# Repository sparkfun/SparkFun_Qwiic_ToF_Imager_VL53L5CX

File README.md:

SparkFun Qwiic ToF Imager with VL53L5CX
========================================

[*SparkFun Qwiic ToF Imager with VL53L5CX(SEN-18642)*](https://www.sparkfun.com/products/18642)

The SparkFun Qwiic ToF Imager is built around VL53L5CX from ST Electronics; a state of the art, Time-of-Flight (ToF), multizone ranging sensor enhancing the ST FlightSense product family. This chip integrates a SPAD array, physical infrared filters, and diffractive optical elements (DOE) to achieve the best ranging performance in various ambient lighting conditions with a range of cover glass materials. Utilizing our handy Qwiic system, no soldering is required to connect it to the rest of your system. However, we still have broken out 0.1"-spaced pins in case you prefer to use a breadboard.

Multizone distance measurements are possible up to 8x8 zones with a wide 63° diagonal FoV which can be reduced by software. Thanks to ST Histogram patented algorithms, the VL53L5CX is able to detect different objects within the FoV. The Histogram also provides immunity to cover glass crosstalk beyond 60 cm.

Ideal for 3D room mapping, obstacle detection for robotics, gesture recognition, IoT, laser-assisted autofocus, and AR/VR enhancement, the Qwiic connector on this sensor makes integration easy. 

SparkFun labored with love to create this code. Feel like supporting open source hardware? 
Buy a [breakout board](https://www.sparkfun.com/products/14722) from SparkFun!

Repository Contents
-------------------

* **/Documents** - Datasheet and User Manual
* **/Hardware** - Eagle design files (.brd, .sch)

Documentation
--------------
* **[Arduino Library](https://github.com/sparkfun/SparkFun_VL53L5CX_Arduino_Library)** - Library for reading distance in millimeters, signal rate, status, etc.
* **[Hookup Guide](https://learn.sparkfun.com/tutorials/qwiic-tof-imager---vl53l5cx-hookup-guide)** - Hookup guide for the Qwiic ToF Imager VL53L5CX

License Information
-------------------

This product is _**open source**_! 

Please review the LICENSE.md file for license information. 

If you have any questions or concerns on licensing, please contact techsupport@sparkfun.com.

Please use, reuse, and modify these files as you see fit. Please maintain attribution to SparkFun Electronics and release any derivative under the same license.

Distributed as-is; no warranty is given.

- Your friends at SparkFun.

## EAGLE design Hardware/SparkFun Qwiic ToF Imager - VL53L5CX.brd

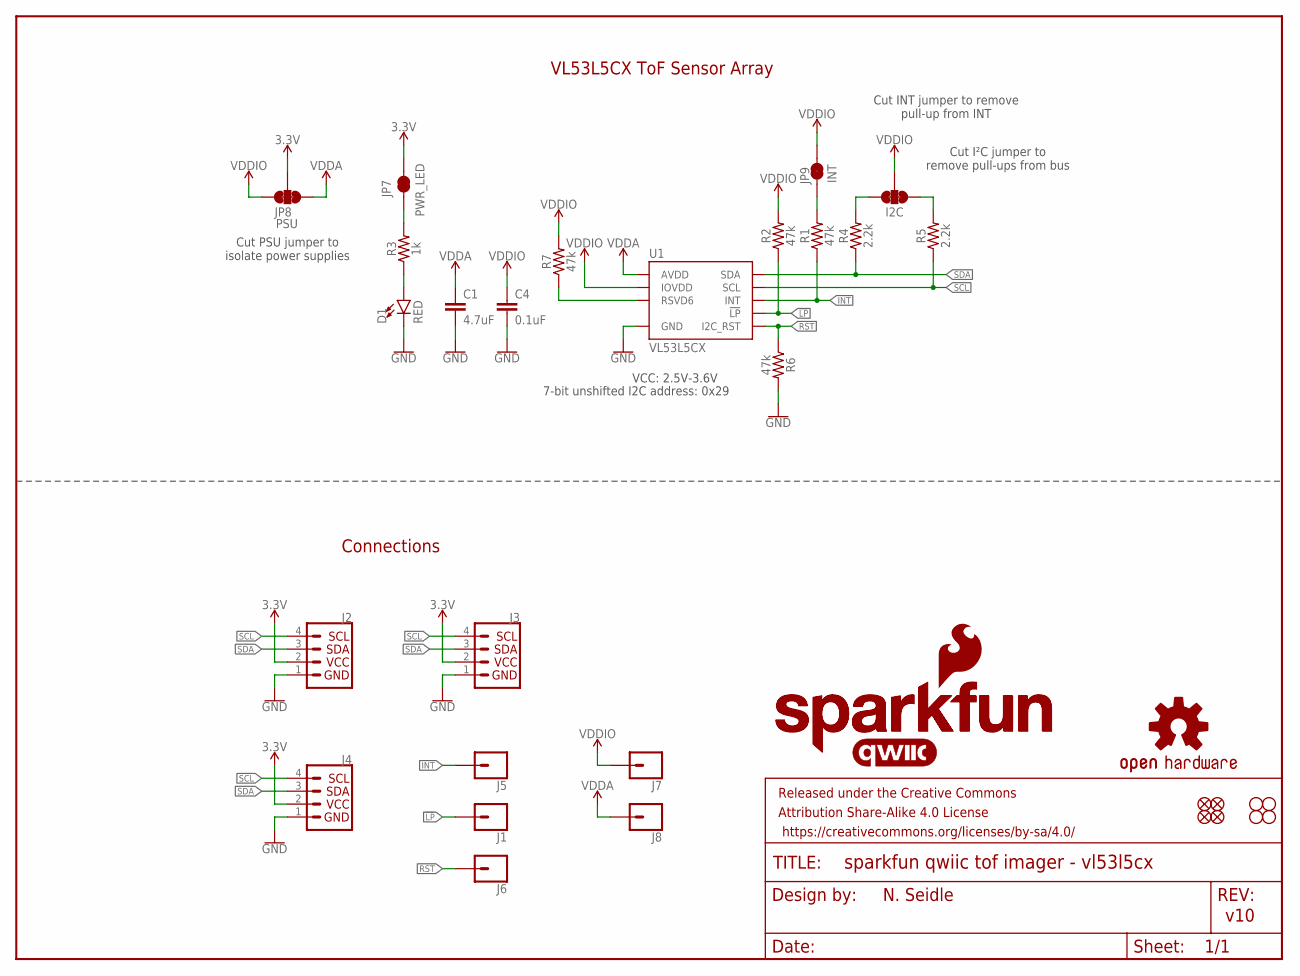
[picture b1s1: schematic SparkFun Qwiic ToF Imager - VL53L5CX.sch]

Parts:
C1: 4.7uF; 0603
C4: 0.1uF; 0603
D1: RED; LED-0603
FRAME1: FRAME-LETTER; CREATIVE_COMMONS
I2C: JUMPER-SMT_3_2-NC_TRACE_SILK; SMT-JUMPER_3_2-NC_TRACE_SILK
J1, J5, J6, J7, J8: CONN_01PTH_NO_SILK_YES_STOP; 1X01_NO_SILK
J2, J4: QWIIC_CONNECTORJS-1MM; JST04_1MM_RA
J3: PTH; 1X04_NO_SILK
JP1, JP2, JP5, JP6: FIDUCIALUFIDUCIAL; MICRO-FIDUCIAL
JP3, JP4, JP10, JP11: STAND-OFF
JP7: PWR_LED; SMT-JUMPER_2_NC_TRACE_SILK
JP8: PSU; SMT-JUMPER_3_2-NC_TRACE_SILK
JP9: INT; SMT-JUMPER_2_NC_TRACE_SILK
LOGO1: OSHW-LOGOMINI; OSHW-LOGO-MINI
LOGO3: QWIIC_LOGO_CONNECTOR; QWIIC_5.5MM
R1, R2, R6, R7: 47k; 0603
R3: 1k; 0603
R4, R5: 2.2k; 0603
U1: VL53L5CX
U$1: SFE_LOGO_NAME.1_INCH; SFE_LOGO_NAME_.1
U$2: SFE_LOGO_NAME_FLAME.1_INCH; SFE_LOGO_NAME_FLAME_.1

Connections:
3.3V: J2.2, J3.2 (VCC), J4.2, JP7.2, JP8.2
!LP: J1.1, R2.1, U1.A5 (!LP)
GND: C1.2, C4.2, D1.C, J2.1, J3.1 (GND), J4.1, R6.2, U1.A2 (GND), U1.A6 (GND), U1.A7 (GND), U1.B4 (GND), U1.C1 (GND), U1.C6 (GND), U1.C7 (GND)
INT: J5.1, R1.1, U1.A3 (INT)
unnamed: I2C.1, R5.2
unnamed: I2C.3, R4.2
unnamed: D1.A, R3.1
unnamed: JP9.1, R1.2
unnamed: JP7.1, R3.2
unnamed: R7.1, U1.C2 (RSVD6)
RST: J6.1, R6.1, U1.A1 (I2C_RST)
SCL: J2.4, J3.4 (SCL), J4.4, R5.1, U1.C4 (SCL)
SDA: J2.3, J3.3 (SDA), J4.3, R4.1, U1.C3 (SDA)
VDDA: C1.1, J8.1, JP8.1, U1.B1 (AVDD), U1.B7 (AVDD)
VDDIO: C4.1, I2C.2, J7.1, JP8.3, JP9.2, R2.2, R7.2, U1.A4 (IOVDD)

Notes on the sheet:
N. Seidle
v10
7-bit unshifted I2C address: 0x29
Cut I²C jumper to remove pull-ups from bus
Cut INT jumper to remove pull-up from INT
VCC: 2.5V-3.6V
VL53L5CX ToF Sensor Array
Cut PSU jumper to isolate power supplies
Connections

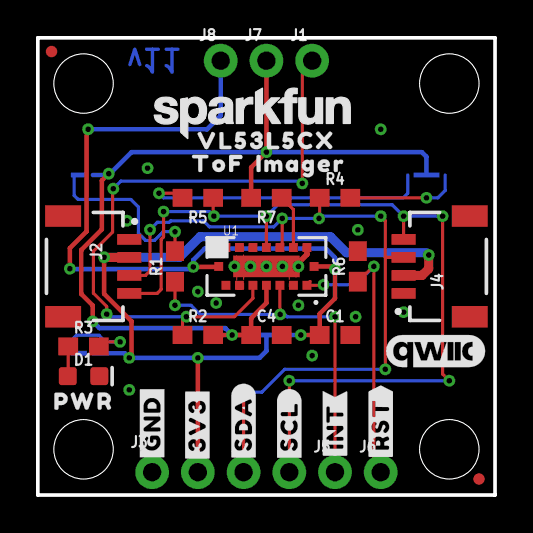
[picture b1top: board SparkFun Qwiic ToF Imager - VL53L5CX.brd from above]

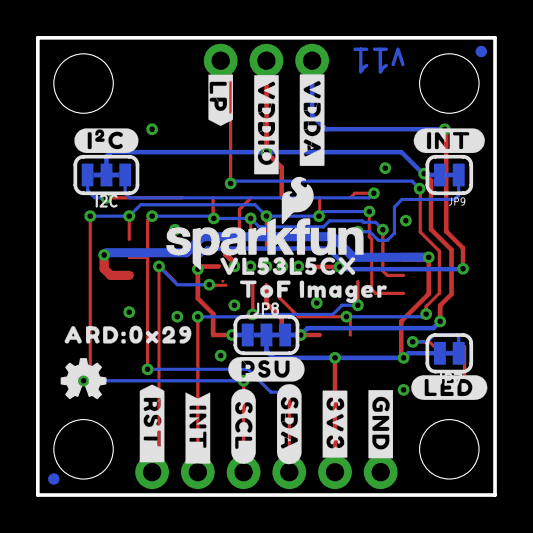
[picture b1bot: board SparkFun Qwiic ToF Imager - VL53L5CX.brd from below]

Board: 2 copper layers, 25.4 x 25.4 mm, 63 parts (25 on the bottom side), 15 nets.

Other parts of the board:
U$3, U$21: #3V3#13
U$4: PWR12
U$5: #LED#10
U$6: #INT#0
U$7: #RST#1
U$8: #INT_#0
U$9: #RST_#1
U$10: ##LP##2
U$11: #INT#1
U$12: #VDDA#0
U$14: #VDDIO#1
U$15: #PSU#0
U$16: #I�C#0
U$17, U$19: VL53L5CX0
U$18, U$22: IMAGER2
U$20, U$23: TOF1
U$24: #SCL#1
U$25: #SDA#0
U$26, U$30: #GND#62130
U$27: ARD#0X290
U$28: #SDA#62131
U$29: #SCL#62132

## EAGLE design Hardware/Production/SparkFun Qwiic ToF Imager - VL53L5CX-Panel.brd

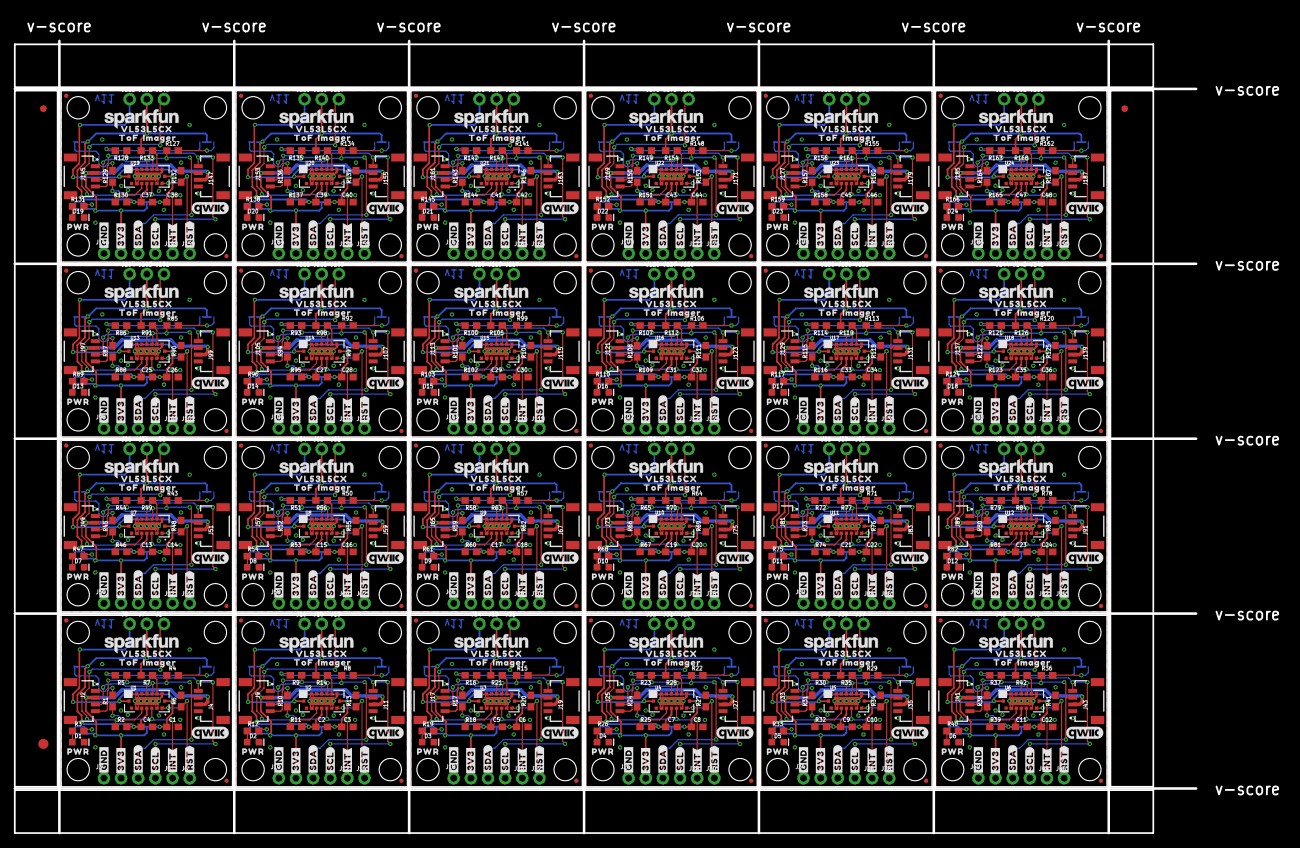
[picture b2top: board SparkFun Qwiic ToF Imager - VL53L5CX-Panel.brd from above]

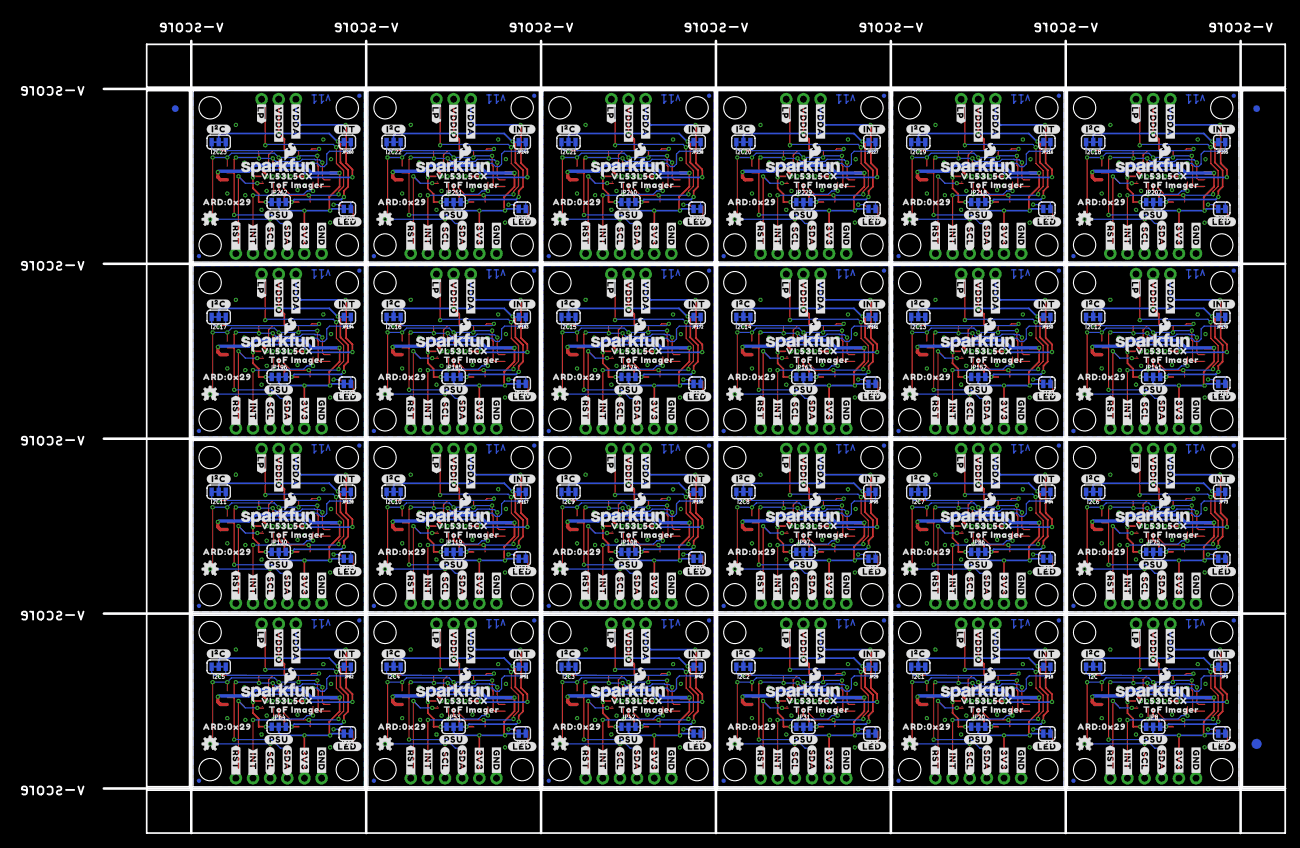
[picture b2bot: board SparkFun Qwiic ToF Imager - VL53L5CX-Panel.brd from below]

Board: 2 copper layers, 188.2 x 121.2 mm, 1494 parts (603 on the bottom side), 360 nets.

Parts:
C1, C3, C6, C8, C10, C12, C14, C16, C18, C20, C22, C24, C26, C28, C30, C32, C34, C36, C38, C40, C42, C44, C46, C48: 4.7uF; 0603
C2, C4, C5, C7, C9, C11, C13, C15, C17, C19, C21, C23, C25, C27, C29, C31, C33, C35, C37, C39, C41, C43, C45, C47: 0.1uF; 0603
D1, D2, D3, D4, D5, D6, D7, D8, D9, D10, D11, D12, D13, D14, D15, D16, D17, D18, D19, D20, D21, D22, D23, D24: RED; LED-0603
E$1, E$2, E$3, E$4: FIDUCIAL-1X2
E$5, E$6: FIDUCIAL-1.5X3
I2C, I2C1, I2C2, I2C3, I2C4, I2C5, I2C6, I2C7, I2C8, I2C9, I2C10, I2C11, I2C12, I2C13, I2C14, I2C15, I2C16, I2C17, I2C18, I2C19, I2C20, I2C21, I2C22, I2C23: JUMPER-SMT_3_2-NC_TRACE_SILK; SMT-JUMPER_3_2-NC_TRACE_SILK
J1, J5, J6, J7, J8, J12, J13, J14, J15, J16, J20, J21, J22, J23, J24, J28, J29, J30, J31, J32, J36, J37, J38, J39, J40, J44, J45, J46, J47, J48, J52, J53, J54, J55, J56, J60, J61, J62, J63, J64, J68, J69, J70, J71, J72, J76, J77, J78, J79, J80, J84, J85, J86, J87, J88, J92, J93, J94, J95, J96, J100, J101, J102, J103, J104, J108, J109, J110, J111, J112, J116, J117, J118, J119, J120, J124, J125, J126, J127, J128, J132, J133, J134, J135, J136, J140, J141, J142, J143, J144, J148, J149, J150, J151, J152, J156, J157, J158, J159, J160, J164, J165, J166, J167, J168, J172, J173, J174, J175, J176, J180, J181, J182, J183, J184, J188, J189, J190, J191, J192: 1X01_NO_SILK
J2, J4, J9, J11, J17, J19, J25, J27, J33, J35, J41, J43, J49, J51, J57, J59, J65, J67, J73, J75, J81, J83, J89, J91, J97, J99, J105, J107, J113, J115, J121, J123, J129, J131, J137, J139, J145, J147, J153, J155, J161, J163, J169, J171, J177, J179, J185, J187: JST04_1MM_RA
J3, J10, J18, J26, J34, J42, J50, J58, J66, J74, J82, J90, J98, J106, J114, J122, J130, J138, J146, J154, J162, J170, J178, J186: PTH; 1X04_NO_SILK
JP1, JP2, JP5, JP6, JP14, JP15, JP16, JP17, JP25, JP26, JP27, JP28, JP36, JP37, JP38, JP39, JP47, JP48, JP49, JP50, JP58, JP59, JP60, JP61, JP69, JP70, JP71, JP72, JP80, JP81, JP82, JP83, JP91, JP92, JP93, JP94, JP102, JP103, JP104, JP105, JP113, JP114, JP115, JP116, JP124, JP125, JP126, JP127, JP135, JP136, JP137, JP138, JP146, JP147, JP148, JP149, JP157, JP158, JP159, JP160, JP168, JP169, JP170, JP171, JP179, JP180, JP181, JP182, JP190, JP191, JP192, JP193, JP201, JP202, JP203, JP204, JP212, JP213, JP214, JP215, JP223, JP224, JP225, JP226, JP234, JP235, JP236, JP237, JP245, JP246, JP247, JP248, JP256, JP257, JP258, JP259: FIDUCIALUFIDUCIAL; MICRO-FIDUCIAL
JP3, JP4, JP10, JP11, JP12, JP13, JP21, JP22, JP23, JP24, JP32, JP33, JP34, JP35, JP43, JP44, JP45, JP46, JP54, JP55, JP56, JP57, JP65, JP66, JP67, JP68, JP76, JP77, JP78, JP79, JP87, JP88, JP89, JP90, JP98, JP99, JP100, JP101, JP109, JP110, JP111, JP112, JP120, JP121, JP122, JP123, JP131, JP132, JP133, JP134, JP142, JP143, JP144, JP145, JP153, JP154, JP155, JP156, JP164, JP165, JP166, JP167, JP175, JP176, JP177, JP178, JP186, JP187, JP188, JP189, JP197, JP198, JP199, JP200, JP208, JP209, JP210, JP211, JP219, JP220, JP221, JP222, JP230, JP231, JP232, JP233, JP241, JP242, JP243, JP244, JP252, JP253, JP254, JP255, JP263, JP264: STAND-OFF
JP7, JP19, JP30, JP41, JP52, JP63, JP74, JP85, JP96, JP107, JP118, JP129, JP140, JP151, JP162, JP173, JP184, JP195, JP206, JP217, JP228, JP239, JP250, JP261: PWR_LED; SMT-JUMPER_2_NC_TRACE_SILK
JP8, JP20, JP31, JP42, JP53, JP64, JP75, JP86, JP97, JP108, JP119, JP130, JP141, JP152, JP163, JP174, JP185, JP196, JP207, JP218, JP229, JP240, JP251, JP262: PSU; SMT-JUMPER_3_2-NC_TRACE_SILK
JP9, JP18, JP29, JP40, JP51, JP62, JP73, JP84, JP95, JP106, JP117, JP128, JP139, JP150, JP161, JP172, JP183, JP194, JP205, JP216, JP227, JP238, JP249, JP260: INT; SMT-JUMPER_2_NC_TRACE_SILK
LOGO1, LOGO2, LOGO5, LOGO7, LOGO9, LOGO11, LOGO13, LOGO15, LOGO17, LOGO19, LOGO21, LOGO23, LOGO25, LOGO27, LOGO29, LOGO31, LOGO33, LOGO35, LOGO37, LOGO39, LOGO41, LOGO43, LOGO45, LOGO47: OSHW-LOGOMINI; OSHW-LOGO-MINI
LOGO3, LOGO4, LOGO6, LOGO8, LOGO10, LOGO12, LOGO14, LOGO16, LOGO18, LOGO20, LOGO22, LOGO24, LOGO26, LOGO28, LOGO30, LOGO32, LOGO34, LOGO36, LOGO38, LOGO40, LOGO42, LOGO44, LOGO46, LOGO48: QWIIC_LOGO_CONNECTOR; QWIIC_5.5MM
R1, R2, R6, R7, R10, R11, R13, R14, R17, R18, R20, R21, R24, R25, R27, R28, R31, R32, R34, R35, R38, R39, R41, R42, R45, R46, R48, R49, R52, R53, R55, R56, R59, R60, R62, R63, R66, R67, R69, R70, R73, R74, R76, R77, R80, R81, R83, R84, R87, R88, R90, R91, R94, R95, R97, R98, R101, R102, R104, R105, R108, R109, R111, R112, R115, R116, R118, R119, R122, R123, R125, R126, R129, R130, R132, R133, R136, R137, R139, R140, R143, R144, R146, R147, R150, R151, R153, R154, R157, R158, R160, R161, R164, R165, R167, R168: 47k; 0603
R3, R12, R19, R26, R33, R40, R47, R54, R61, R68, R75, R82, R89, R96, R103, R110, R117, R124, R131, R138, R145, R152, R159, R166: 1k; 0603
R4, R5, R8, R9, R15, R16, R22, R23, R29, R30, R36, R37, R43, R44, R50, R51, R57, R58, R64, R65, R71, R72, R78, R79, R85, R86, R92, R93, R99, R100, R106, R107, R113, R114, R120, R121, R127, R128, R134, R135, R141, R142, R148, R149, R155, R156, R162, R163: 2.2k; 0603
U1, U2, U3, U4, U5, U6, U7, U8, U9, U10, U11, U12, U13, U14, U15, U16, U17, U18, U19, U20, U21, U22, U23, U24: VL53L5CX
U$1, U$31, U$60, U$89, U$118, U$147, U$176, U$205, U$234, U$263, U$292, U$321, U$350, U$379, U$408, U$437, U$466, U$495, U$524, U$553, U$582, U$611, U$640, U$669: SFE_LOGO_NAME.1_INCH; SFE_LOGO_NAME_.1
U$2, U$13, U$59, U$88, U$117, U$146, U$175, U$204, U$233, U$262, U$291, U$320, U$349, U$378, U$407, U$436, U$465, U$494, U$523, U$552, U$581, U$610, U$639, U$668: SFE_LOGO_NAME_FLAME.1_INCH; SFE_LOGO_NAME_FLAME_.1
U$3, U$21, U$36, U$37, U$65, U$66, U$94, U$95, U$123, U$124, U$152, U$153, U$181, U$182, U$210, U$211, U$239, U$240, U$268, U$269, U$297, U$298, U$326, U$327, U$355, U$356, U$384, U$385, U$413, U$414, U$442, U$443, U$471, U$472, U$500, U$501, U$529, U$530, U$558, U$559, U$587, U$588, U$616, U$617, U$645, U$646, U$674, U$675: #3V3#13
U$4, U$38, U$67, U$96, U$125, U$154, U$183, U$212, U$241, U$270, U$299, U$328, U$357, U$386, U$415, U$444, U$473, U$502, U$531, U$560, U$589, U$618, U$647, U$676: PWR12
U$5, U$39, U$68, U$97, U$126, U$155, U$184, U$213, U$242, U$271, U$300, U$329, U$358, U$387, U$416, U$445, U$474, U$503, U$532, U$561, U$590, U$619, U$648, U$677: #LED#10
U$6, U$40, U$69, U$98, U$127, U$156, U$185, U$214, U$243, U$272, U$301, U$330, U$359, U$388, U$417, U$446, U$475, U$504, U$533, U$562, U$591, U$620, U$649, U$678: #INT#0
U$7, U$41, U$70, U$99, U$128, U$157, U$186, U$215, U$244, U$273, U$302, U$331, U$360, U$389, U$418, U$447, U$476, U$505, U$534, U$563, U$592, U$621, U$650, U$679: #RST#1
U$8, U$42, U$71, U$100, U$129, U$158, U$187, U$216, U$245, U$274, U$303, U$332, U$361, U$390, U$419, U$448, U$477, U$506, U$535, U$564, U$593, U$622, U$651, U$680: #INT_#0
U$9, U$43, U$72, U$101, U$130, U$159, U$188, U$217, U$246, U$275, U$304, U$333, U$362, U$391, U$420, U$449, U$478, U$507, U$536, U$565, U$594, U$623, U$652, U$681: #RST_#1
U$10, U$44, U$73, U$102, U$131, U$160, U$189, U$218, U$247, U$276, U$305, U$334, U$363, U$392, U$421, U$450, U$479, U$508, U$537, U$566, U$595, U$624, U$653, U$682: ##LP##2
U$11, U$51, U$80, U$109, U$138, U$167, U$196, U$225, U$254, U$283, U$312, U$341, U$370, U$399, U$428, U$457, U$486, U$515, U$544, U$573, U$602, U$631, U$660, U$689: #INT#1
U$12, U$45, U$74, U$103, U$132, U$161, U$190, U$219, U$248, U$277, U$306, U$335, U$364, U$393, U$422, U$451, U$480, U$509, U$538, U$567, U$596, U$625, U$654, U$683: #VDDA#0
U$14, U$46, U$75, U$104, U$133, U$162, U$191, U$220, U$249, U$278, U$307, U$336, U$365, U$394, U$423, U$452, U$481, U$510, U$539, U$568, U$597, U$626, U$655, U$684: #VDDIO#1
U$15, U$52, U$81, U$110, U$139, U$168, U$197, U$226, U$255, U$284, U$313, U$342, U$371, U$400, U$429, U$458, U$487, U$516, U$545, U$574, U$603, U$632, U$661, U$690: #PSU#0
U$16, U$50, U$79, U$108, U$137, U$166, U$195, U$224, U$253, U$282, U$311, U$340, U$369, U$398, U$427, U$456, U$485, U$514, U$543, U$572, U$601, U$630, U$659, U$688: #I�C#0
U$17, U$19, U$47, U$53, U$76, U$82, U$105, U$111, U$134, U$140, U$163, U$169, U$192, U$198, U$221, U$227, U$250, U$256, U$279, U$285, U$308, U$314, U$337, U$343, U$366, U$372, U$395, U$401, U$424, U$430, U$453, U$459, U$482, U$488, U$511, U$517, U$540, U$546, U$569, U$575, U$598, U$604, U$627, U$633, U$656, U$662, U$685, U$691: VL53L5CX0
U$18, U$22, U$48, U$55, U$77, U$84, U$106, U$113, U$135, U$142, U$164, U$171, U$193, U$200, U$222, U$229, U$251, U$258, U$280, U$287, U$309, U$316, U$338, U$345, U$367, U$374, U$396, U$403, U$425, U$432, U$454, U$461, U$483, U$490, U$512, U$519, U$541, U$548, U$570, U$577, U$599, U$606, U$628, U$635, U$657, U$664, U$686, U$693: IMAGER2
U$20, U$23, U$49, U$54, U$78, U$83, U$107, U$112, U$136, U$141, U$165, U$170, U$194, U$199, U$223, U$228, U$252, U$257, U$281, U$286, U$310, U$315, U$339, U$344, U$368, U$373, U$397, U$402, U$426, U$431, U$455, U$460, U$484, U$489, U$513, U$518, U$542, U$547, U$571, U$576, U$600, U$605, U$629, U$634, U$658, U$663, U$687, U$692: TOF1
U$24, U$56, U$85, U$114, U$143, U$172, U$201, U$230, U$259, U$288, U$317, U$346, U$375, U$404, U$433, U$462, U$491, U$520, U$549, U$578, U$607, U$636, U$665, U$694: #SCL#1
U$25, U$57, U$86, U$115, U$144, U$173, U$202, U$231, U$260, U$289, U$318, U$347, U$376, U$405, U$434, U$463, U$492, U$521, U$550, U$579, U$608, U$637, U$666, U$695: #SDA#0
U$26, U$30, U$32, U$35, U$61, U$64, U$90, U$93, U$119, U$122, U$148, U$151, U$177, U$180, U$206, U$209, U$235, U$238, U$264, U$267, U$293, U$296, U$322, U$325, U$351, U$354, U$380, U$383, U$409, U$412, U$438, U$441, U$467, U$470, U$496, U$499, U$525, U$528, U$554, U$557, U$583, U$586, U$612, U$615, U$641, U$644, U$670, U$673: #GND#62130
U$27, U$58, U$87, U$116, U$145, U$174, U$203, U$232, U$261, U$290, U$319, U$348, U$377, U$406, U$435, U$464, U$493, U$522, U$551, U$580, U$609, U$638, U$667, U$696: ARD#0X290
U$28, U$33, U$62, U$91, U$120, U$149, U$178, U$207, U$236, U$265, U$294, U$323, U$352, U$381, U$410, U$439, U$468, U$497, U$526, U$555, U$584, U$613, U$642, U$671: #SDA#62131
U$29, U$34, U$63, U$92, U$121, U$150, U$179, U$208, U$237, U$266, U$295, U$324, U$353, U$382, U$411, U$440, U$469, U$498, U$527, U$556, U$585, U$614, U$643, U$672: #SCL#62132

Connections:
3.3V: J2.2, J3.2, J4.2, JP7.2, JP8.2
3.3V1: J9.2, J10.2, J11.2, JP19.2, JP20.2
3.3V2: J17.2, J18.2, J19.2, JP30.2, JP31.2
3.3V3: J25.2, J26.2, J27.2, JP41.2, JP42.2
3.3V4: J33.2, J34.2, J35.2, JP52.2, JP53.2
3.3V5: J41.2, J42.2, J43.2, JP63.2, JP64.2
3.3V6: J49.2, J50.2, J51.2, JP74.2, JP75.2
3.3V7: J57.2, J58.2, J59.2, JP85.2, JP86.2
3.3V8: J65.2, J66.2, J67.2, JP96.2, JP97.2
3.3V9: J73.2, J74.2, J75.2, JP107.2, JP108.2
3.3V10: J81.2, J82.2, J83.2, JP118.2, JP119.2
3.3V11: J89.2, J90.2, J91.2, JP129.2, JP130.2
3.3V12: J97.2, J98.2, J99.2, JP140.2, JP141.2
3.3V13: J105.2, J106.2, J107.2, JP151.2, JP152.2
3.3V14: J113.2, J114.2, J115.2, JP162.2, JP163.2
3.3V15: J121.2, J122.2, J123.2, JP173.2, JP174.2
3.3V16: J129.2, J130.2, J131.2, JP184.2, JP185.2
3.3V17: J137.2, J138.2, J139.2, JP195.2, JP196.2
3.3V18: J145.2, J146.2, J147.2, JP206.2, JP207.2
3.3V19: J153.2, J154.2, J155.2, JP217.2, JP218.2
3.3V20: J161.2, J162.2, J163.2, JP228.2, JP229.2
3.3V21: J169.2, J170.2, J171.2, JP239.2, JP240.2
3.3V22: J177.2, J178.2, J179.2, JP250.2, JP251.2
3.3V23: J185.2, J186.2, J187.2, JP261.2, JP262.2
!LP: J1.1, R2.1, U1.A5
!LP1: J13.1, R11.1, U2.A5
!LP2: J21.1, R18.1, U3.A5
!LP3: J29.1, R25.1, U4.A5
!LP4: J37.1, R32.1, U5.A5
!LP5: J45.1, R39.1, U6.A5
!LP6: J53.1, R46.1, U7.A5
!LP7: J61.1, R53.1, U8.A5
!LP8: J69.1, R60.1, U9.A5
!LP9: J77.1, R67.1, U10.A5
!LP10: J85.1, R74.1, U11.A5
!LP11: J93.1, R81.1, U12.A5
!LP12: J101.1, R88.1, U13.A5
!LP13: J109.1, R95.1, U14.A5
!LP14: J117.1, R102.1, U15.A5
!LP15: J125.1, R109.1, U16.A5
!LP16: J133.1, R116.1, U17.A5
!LP17: J141.1, R123.1, U18.A5
!LP18: J149.1, R130.1, U19.A5
!LP19: J157.1, R137.1, U20.A5
!LP20: J165.1, R144.1, U21.A5
!LP21: J173.1, R151.1, U22.A5
!LP22: J181.1, R158.1, U23.A5
!LP23: J189.1, R165.1, U24.A5
GND: C1.2, C4.2, D1.C, J2.1, J3.1, J4.1, R6.2, U1.A2, U1.A6, U1.A7, U1.B4, U1.C1, U1.C6, U1.C7
GND1: C2.2, C3.2, D2.C, J9.1, J10.1, J11.1, R13.2, U2.A2, U2.A6, U2.A7, U2.B4, U2.C1, U2.C6, U2.C7
GND2: C5.2, C6.2, D3.C, J17.1, J18.1, J19.1, R20.2, U3.A2, U3.A6, U3.A7, U3.B4, U3.C1, U3.C6, U3.C7
GND3: C7.2, C8.2, D4.C, J25.1, J26.1, J27.1, R27.2, U4.A2, U4.A6, U4.A7, U4.B4, U4.C1, U4.C6, U4.C7
GND4: C9.2, C10.2, D5.C, J33.1, J34.1, J35.1, R34.2, U5.A2, U5.A6, U5.A7, U5.B4, U5.C1, U5.C6, U5.C7
GND5: C11.2, C12.2, D6.C, J41.1, J42.1, J43.1, R41.2, U6.A2, U6.A6, U6.A7, U6.B4, U6.C1, U6.C6, U6.C7
GND6: C13.2, C14.2, D7.C, J49.1, J50.1, J51.1, R48.2, U7.A2, U7.A6, U7.A7, U7.B4, U7.C1, U7.C6, U7.C7
GND7: C15.2, C16.2, D8.C, J57.1, J58.1, J59.1, R55.2, U8.A2, U8.A6, U8.A7, U8.B4, U8.C1, U8.C6, U8.C7
GND8: C17.2, C18.2, D9.C, J65.1, J66.1, J67.1, R62.2, U9.A2, U9.A6, U9.A7, U9.B4, U9.C1, U9.C6, U9.C7
GND9: C19.2, C20.2, D10.C, J73.1, J74.1, J75.1, R69.2, U10.A2, U10.A6, U10.A7, U10.B4, U10.C1, U10.C6, U10.C7
GND10: C21.2, C22.2, D11.C, J81.1, J82.1, J83.1, R76.2, U11.A2, U11.A6, U11.A7, U11.B4, U11.C1, U11.C6, U11.C7
GND11: C23.2, C24.2, D12.C, J89.1, J90.1, J91.1, R83.2, U12.A2, U12.A6, U12.A7, U12.B4, U12.C1, U12.C6, U12.C7
GND12: C25.2, C26.2, D13.C, J97.1, J98.1, J99.1, R90.2, U13.A2, U13.A6, U13.A7, U13.B4, U13.C1, U13.C6, U13.C7
GND13: C27.2, C28.2, D14.C, J105.1, J106.1, J107.1, R97.2, U14.A2, U14.A6, U14.A7, U14.B4, U14.C1, U14.C6, U14.C7
GND14: C29.2, C30.2, D15.C, J113.1, J114.1, J115.1, R104.2, U15.A2, U15.A6, U15.A7, U15.B4, U15.C1, U15.C6, U15.C7
GND15: C31.2, C32.2, D16.C, J121.1, J122.1, J123.1, R111.2, U16.A2, U16.A6, U16.A7, U16.B4, U16.C1, U16.C6, U16.C7
GND16: C33.2, C34.2, D17.C, J129.1, J130.1, J131.1, R118.2, U17.A2, U17.A6, U17.A7, U17.B4, U17.C1, U17.C6, U17.C7
GND17: C35.2, C36.2, D18.C, J137.1, J138.1, J139.1, R125.2, U18.A2, U18.A6, U18.A7, U18.B4, U18.C1, U18.C6, U18.C7
GND18: C37.2, C38.2, D19.C, J145.1, J146.1, J147.1, R132.2, U19.A2, U19.A6, U19.A7, U19.B4, U19.C1, U19.C6, U19.C7
GND19: C39.2, C40.2, D20.C, J153.1, J154.1, J155.1, R139.2, U20.A2, U20.A6, U20.A7, U20.B4, U20.C1, U20.C6, U20.C7
GND20: C41.2, C42.2, D21.C, J161.1, J162.1, J163.1, R146.2, U21.A2, U21.A6, U21.A7, U21.B4, U21.C1, U21.C6, U21.C7
GND21: C43.2, C44.2, D22.C, J169.1, J170.1, J171.1, R153.2, U22.A2, U22.A6, U22.A7, U22.B4, U22.C1, U22.C6, U22.C7
GND22: C45.2, C46.2, D23.C, J177.1, J178.1, J179.1, R160.2, U23.A2, U23.A6, U23.A7, U23.B4, U23.C1, U23.C6, U23.C7
GND23: C47.2, C48.2, D24.C, J185.1, J186.1, J187.1, R167.2, U24.A2, U24.A6, U24.A7, U24.B4, U24.C1, U24.C6, U24.C7
INT: J5.1, R1.1, U1.A3
INT1: J12.1, R10.1, U2.A3
INT2: J20.1, R17.1, U3.A3
INT3: J28.1, R24.1, U4.A3
INT4: J36.1, R31.1, U5.A3
INT5: J44.1, R38.1, U6.A3
INT6: J52.1, R45.1, U7.A3
INT7: J60.1, R52.1, U8.A3
INT8: J68.1, R59.1, U9.A3
INT9: J76.1, R66.1, U10.A3
INT10: J84.1, R73.1, U11.A3
INT11: J92.1, R80.1, U12.A3
INT12: J100.1, R87.1, U13.A3
INT13: J108.1, R94.1, U14.A3
INT14: J116.1, R101.1, U15.A3
INT15: J124.1, R108.1, U16.A3
INT16: J132.1, R115.1, U17.A3
INT17: J140.1, R122.1, U18.A3
INT18: J148.1, R129.1, U19.A3
INT19: J156.1, R136.1, U20.A3
INT20: J164.1, R143.1, U21.A3
INT21: J172.1, R150.1, U22.A3
INT22: J180.1, R157.1, U23.A3
INT23: J188.1, R164.1, U24.A3
unnamed: I2C.1, R5.2
unnamed: I2C.3, R4.2
unnamed: D1.A, R3.1
unnamed: JP9.1, R1.2
unnamed: JP7.1, R3.2
unnamed: R7.1, U1.C2
unnamed: I2C1.1, R9.2
unnamed: I2C1.3, R8.2
unnamed: JP18.1, R10.2
unnamed: D2.A, R12.1
unnamed: JP19.1, R12.2
unnamed: R14.1, U2.C2
unnamed: I2C2.1, R16.2
unnamed: I2C2.3, R15.2
unnamed: JP29.1, R17.2
unnamed: D3.A, R19.1
unnamed: JP30.1, R19.2
unnamed: R21.1, U3.C2
unnamed: I2C3.1, R23.2
unnamed: I2C3.3, R22.2
unnamed: JP40.1, R24.2
unnamed: D4.A, R26.1
unnamed: JP41.1, R26.2
unnamed: R28.1, U4.C2
unnamed: I2C4.1, R30.2
unnamed: I2C4.3, R29.2
unnamed: JP51.1, R31.2
unnamed: D5.A, R33.1
unnamed: JP52.1, R33.2
unnamed: R35.1, U5.C2
unnamed: I2C5.1, R37.2
unnamed: I2C5.3, R36.2
unnamed: JP62.1, R38.2
unnamed: D6.A, R40.1
unnamed: JP63.1, R40.2
unnamed: R42.1, U6.C2
unnamed: I2C6.1, R44.2
unnamed: I2C6.3, R43.2
unnamed: JP73.1, R45.2
unnamed: D7.A, R47.1
unnamed: JP74.1, R47.2
unnamed: R49.1, U7.C2
unnamed: I2C7.1, R51.2
unnamed: I2C7.3, R50.2
unnamed: JP84.1, R52.2
unnamed: D8.A, R54.1
unnamed: JP85.1, R54.2
unnamed: R56.1, U8.C2
unnamed: I2C8.1, R58.2
unnamed: I2C8.3, R57.2
unnamed: JP95.1, R59.2
unnamed: D9.A, R61.1
unnamed: JP96.1, R61.2
unnamed: R63.1, U9.C2
unnamed: I2C9.1, R65.2
unnamed: I2C9.3, R64.2
unnamed: JP106.1, R66.2
unnamed: D10.A, R68.1
unnamed: JP107.1, R68.2
unnamed: R70.1, U10.C2
unnamed: I2C10.1, R72.2
unnamed: I2C10.3, R71.2
unnamed: JP117.1, R73.2
unnamed: D11.A, R75.1
unnamed: JP118.1, R75.2
unnamed: R77.1, U11.C2
unnamed: I2C11.1, R79.2
unnamed: I2C11.3, R78.2
unnamed: JP128.1, R80.2
unnamed: D12.A, R82.1
unnamed: JP129.1, R82.2
unnamed: R84.1, U12.C2
unnamed: I2C12.1, R86.2
unnamed: I2C12.3, R85.2
unnamed: JP139.1, R87.2
unnamed: D13.A, R89.1
unnamed: JP140.1, R89.2
unnamed: R91.1, U13.C2
unnamed: I2C13.1, R93.2
unnamed: I2C13.3, R92.2
unnamed: JP150.1, R94.2
unnamed: D14.A, R96.1
unnamed: JP151.1, R96.2
unnamed: R98.1, U14.C2
unnamed: I2C14.1, R100.2
unnamed: I2C14.3, R99.2
unnamed: JP161.1, R101.2
unnamed: D15.A, R103.1
unnamed: JP162.1, R103.2
unnamed: R105.1, U15.C2
unnamed: I2C15.1, R107.2
unnamed: I2C15.3, R106.2
unnamed: JP172.1, R108.2
unnamed: D16.A, R110.1
unnamed: JP173.1, R110.2
unnamed: R112.1, U16.C2
unnamed: I2C16.1, R114.2
unnamed: I2C16.3, R113.2
unnamed: JP183.1, R115.2
unnamed: D17.A, R117.1
unnamed: JP184.1, R117.2
unnamed: R119.1, U17.C2
unnamed: I2C17.1, R121.2
unnamed: I2C17.3, R120.2
unnamed: JP194.1, R122.2
unnamed: D18.A, R124.1
unnamed: JP195.1, R124.2
unnamed: R126.1, U18.C2
unnamed: I2C18.1, R128.2
unnamed: I2C18.3, R127.2
unnamed: JP205.1, R129.2
unnamed: D19.A, R131.1
unnamed: JP206.1, R131.2
unnamed: R133.1, U19.C2
unnamed: I2C19.1, R135.2
unnamed: I2C19.3, R134.2
unnamed: JP216.1, R136.2
unnamed: D20.A, R138.1
unnamed: JP217.1, R138.2
unnamed: R140.1, U20.C2
unnamed: I2C20.1, R142.2
unnamed: I2C20.3, R141.2
unnamed: JP227.1, R143.2
unnamed: D21.A, R145.1
unnamed: JP228.1, R145.2
unnamed: R147.1, U21.C2
unnamed: I2C21.1, R149.2
unnamed: I2C21.3, R148.2
unnamed: JP238.1, R150.2
unnamed: D22.A, R152.1
unnamed: JP239.1, R152.2
unnamed: R154.1, U22.C2
unnamed: I2C22.1, R156.2
unnamed: I2C22.3, R155.2
unnamed: JP249.1, R157.2
unnamed: D23.A, R159.1
unnamed: JP250.1, R159.2
unnamed: R161.1, U23.C2
unnamed: I2C23.1, R163.2
unnamed: I2C23.3, R162.2
unnamed: JP260.1, R164.2
unnamed: D24.A, R166.1
unnamed: JP261.1, R166.2
unnamed: R168.1, U24.C2
RST: J6.1, R6.1, U1.A1
RST1: J14.1, R13.1, U2.A1
RST2: J22.1, R20.1, U3.A1
RST3: J30.1, R27.1, U4.A1
RST4: J38.1, R34.1, U5.A1
RST5: J46.1, R41.1, U6.A1
RST6: J54.1, R48.1, U7.A1
RST7: J62.1, R55.1, U8.A1
RST8: J70.1, R62.1, U9.A1
RST9: J78.1, R69.1, U10.A1
RST10: J86.1, R76.1, U11.A1
RST11: J94.1, R83.1, U12.A1
RST12: J102.1, R90.1, U13.A1
RST13: J110.1, R97.1, U14.A1
RST14: J118.1, R104.1, U15.A1
RST15: J126.1, R111.1, U16.A1
RST16: J134.1, R118.1, U17.A1
RST17: J142.1, R125.1, U18.A1
RST18: J150.1, R132.1, U19.A1
RST19: J158.1, R139.1, U20.A1
RST20: J166.1, R146.1, U21.A1
RST21: J174.1, R153.1, U22.A1
RST22: J182.1, R160.1, U23.A1
RST23: J190.1, R167.1, U24.A1
SCL: J2.4, J3.4, J4.4, R5.1, U1.C4
SCL1: J9.4, J10.4, J11.4, R9.1, U2.C4
SCL2: J17.4, J18.4, J19.4, R16.1, U3.C4
SCL3: J25.4, J26.4, J27.4, R23.1, U4.C4
SCL4: J33.4, J34.4, J35.4, R30.1, U5.C4
SCL5: J41.4, J42.4, J43.4, R37.1, U6.C4
SCL6: J49.4, J50.4, J51.4, R44.1, U7.C4
SCL7: J57.4, J58.4, J59.4, R51.1, U8.C4
SCL8: J65.4, J66.4, J67.4, R58.1, U9.C4
SCL9: J73.4, J74.4, J75.4, R65.1, U10.C4
SCL10: J81.4, J82.4, J83.4, R72.1, U11.C4
SCL11: J89.4, J90.4, J91.4, R79.1, U12.C4
SCL12: J97.4, J98.4, J99.4, R86.1, U13.C4
SCL13: J105.4, J106.4, J107.4, R93.1, U14.C4
SCL14: J113.4, J114.4, J115.4, R100.1, U15.C4
SCL15: J121.4, J122.4, J123.4, R107.1, U16.C4
SCL16: J129.4, J130.4, J131.4, R114.1, U17.C4
SCL17: J137.4, J138.4, J139.4, R121.1, U18.C4
SCL18: J145.4, J146.4, J147.4, R128.1, U19.C4
SCL19: J153.4, J154.4, J155.4, R135.1, U20.C4
SCL20: J161.4, J162.4, J163.4, R142.1, U21.C4
SCL21: J169.4, J170.4, J171.4, R149.1, U22.C4
SCL22: J177.4, J178.4, J179.4, R156.1, U23.C4
SCL23: J185.4, J186.4, J187.4, R163.1, U24.C4
SDA: J2.3, J3.3, J4.3, R4.1, U1.C3
SDA1: J9.3, J10.3, J11.3, R8.1, U2.C3
SDA2: J17.3, J18.3, J19.3, R15.1, U3.C3
SDA3: J25.3, J26.3, J27.3, R22.1, U4.C3
SDA4: J33.3, J34.3, J35.3, R29.1, U5.C3
SDA5: J41.3, J42.3, J43.3, R36.1, U6.C3
SDA6: J49.3, J50.3, J51.3, R43.1, U7.C3
SDA7: J57.3, J58.3, J59.3, R50.1, U8.C3
SDA8: J65.3, J66.3, J67.3, R57.1, U9.C3
SDA9: J73.3, J74.3, J75.3, R64.1, U10.C3
SDA10: J81.3, J82.3, J83.3, R71.1, U11.C3
SDA11: J89.3, J90.3, J91.3, R78.1, U12.C3
SDA12: J97.3, J98.3, J99.3, R85.1, U13.C3
SDA13: J105.3, J106.3, J107.3, R92.1, U14.C3
SDA14: J113.3, J114.3, J115.3, R99.1, U15.C3
SDA15: J121.3, J122.3, J123.3, R106.1, U16.C3
SDA16: J129.3, J130.3, J131.3, R113.1, U17.C3
SDA17: J137.3, J138.3, J139.3, R120.1, U18.C3
SDA18: J145.3, J146.3, J147.3, R127.1, U19.C3
SDA19: J153.3, J154.3, J155.3, R134.1, U20.C3
SDA20: J161.3, J162.3, J163.3, R141.1, U21.C3
SDA21: J169.3, J170.3, J171.3, R148.1, U22.C3
SDA22: J177.3, J178.3, J179.3, R155.1, U23.C3
SDA23: J185.3, J186.3, J187.3, R162.1, U24.C3
VDDA: C1.1, J8.1, JP8.1, U1.B1, U1.B7
VDDA1: C3.1, J16.1, JP20.1, U2.B1, U2.B7
VDDA2: C6.1, J24.1, JP31.1, U3.B1, U3.B7
VDDA3: C8.1, J32.1, JP42.1, U4.B1, U4.B7
VDDA4: C10.1, J40.1, JP53.1, U5.B1, U5.B7
VDDA5: C12.1, J48.1, JP64.1, U6.B1, U6.B7
VDDA6: C14.1, J56.1, JP75.1, U7.B1, U7.B7
VDDA7: C16.1, J64.1, JP86.1, U8.B1, U8.B7
VDDA8: C18.1, J72.1, JP97.1, U9.B1, U9.B7
VDDA9: C20.1, J80.1, JP108.1, U10.B1, U10.B7
VDDA10: C22.1, J88.1, JP119.1, U11.B1, U11.B7
VDDA11: C24.1, J96.1, JP130.1, U12.B1, U12.B7
VDDA12: C26.1, J104.1, JP141.1, U13.B1, U13.B7
VDDA13: C28.1, J112.1, JP152.1, U14.B1, U14.B7
VDDA14: C30.1, J120.1, JP163.1, U15.B1, U15.B7
VDDA15: C32.1, J128.1, JP174.1, U16.B1, U16.B7
VDDA16: C34.1, J136.1, JP185.1, U17.B1, U17.B7
VDDA17: C36.1, J144.1, JP196.1, U18.B1, U18.B7
VDDA18: C38.1, J152.1, JP207.1, U19.B1, U19.B7
VDDA19: C40.1, J160.1, JP218.1, U20.B1, U20.B7
VDDA20: C42.1, J168.1, JP229.1, U21.B1, U21.B7
VDDA21: C44.1, J176.1, JP240.1, U22.B1, U22.B7
VDDA22: C46.1, J184.1, JP251.1, U23.B1, U23.B7
VDDA23: C48.1, J192.1, JP262.1, U24.B1, U24.B7
VDDIO: C4.1, I2C.2, J7.1, JP8.3, JP9.2, R2.2, R7.2, U1.A4
VDDIO1: C2.1, I2C1.2, J15.1, JP18.2, JP20.3, R11.2, R14.2, U2.A4
VDDIO2: C5.1, I2C2.2, J23.1, JP29.2, JP31.3, R18.2, R21.2, U3.A4
VDDIO3: C7.1, I2C3.2, J31.1, JP40.2, JP42.3, R25.2, R28.2, U4.A4
VDDIO4: C9.1, I2C4.2, J39.1, JP51.2, JP53.3, R32.2, R35.2, U5.A4
VDDIO5: C11.1, I2C5.2, J47.1, JP62.2, JP64.3, R39.2, R42.2, U6.A4
VDDIO6: C13.1, I2C6.2, J55.1, JP73.2, JP75.3, R46.2, R49.2, U7.A4
VDDIO7: C15.1, I2C7.2, J63.1, JP84.2, JP86.3, R53.2, R56.2, U8.A4
VDDIO8: C17.1, I2C8.2, J71.1, JP95.2, JP97.3, R60.2, R63.2, U9.A4
VDDIO9: C19.1, I2C9.2, J79.1, JP106.2, JP108.3, R67.2, R70.2, U10.A4
VDDIO10: C21.1, I2C10.2, J87.1, JP117.2, JP119.3, R74.2, R77.2, U11.A4
VDDIO11: C23.1, I2C11.2, J95.1, JP128.2, JP130.3, R81.2, R84.2, U12.A4
VDDIO12: C25.1, I2C12.2, J103.1, JP139.2, JP141.3, R88.2, R91.2, U13.A4
VDDIO13: C27.1, I2C13.2, J111.1, JP150.2, JP152.3, R95.2, R98.2, U14.A4
VDDIO14: C29.1, I2C14.2, J119.1, JP161.2, JP163.3, R102.2, R105.2, U15.A4
VDDIO15: C31.1, I2C15.2, J127.1, JP172.2, JP174.3, R109.2, R112.2, U16.A4
VDDIO16: C33.1, I2C16.2, J135.1, JP183.2, JP185.3, R116.2, R119.2, U17.A4
VDDIO17: C35.1, I2C17.2, J143.1, JP194.2, JP196.3, R123.2, R126.2, U18.A4
VDDIO18: C37.1, I2C18.2, J151.1, JP205.2, JP207.3, R130.2, R133.2, U19.A4
VDDIO19: C39.1, I2C19.2, J159.1, JP216.2, JP218.3, R137.2, R140.2, U20.A4
VDDIO20: C41.1, I2C20.2, J167.1, JP227.2, JP229.3, R144.2, R147.2, U21.A4
VDDIO21: C43.1, I2C21.2, J175.1, JP238.2, JP240.3, R151.2, R154.2, U22.A4
VDDIO22: C45.1, I2C22.2, J183.1, JP249.2, JP251.3, R158.2, R161.2, U23.A4
VDDIO23: C47.1, I2C23.2, J191.1, JP260.2, JP262.3, R165.2, R168.2, U24.A4

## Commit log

2021-09-14 Add PROD_ID to IC
2021-09-20 Add production files post design review
2021-11-04 Reduce copper and paste aperatures on VL53L5CX FP.
2021-11-18 Fix I2C address in schematic.
2022-08-16 Add panel files for v1.1

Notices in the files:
parts and their libraries:
SparkFun-Resistors: Licensing: Creative Commons ShareAlike 4.0 International - https://creativecommons.org/licenses/by-sa/4.0
SparkFun-Aesthetics: Released under the Creative Commons Attribution Share-Alike 4.0 License
SparkFun-Aesthetics: https://creativecommons.org/licenses/by-sa/4.0
